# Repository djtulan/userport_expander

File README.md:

# Userport Expander
C64 Userport Expander is a remake of a project from a "64'er Sonderheft" magazine.

You can find the scan (german language) [here](./docs/UP%2024%20Leitungen_k.pdf).

The driver software can be found [here](./Software/SH67.zip).

The C64 Userport Expander expands the C64 Userport from 8 Bit to 3x8bit.

## 3D Model

## Real Picture

## Layout and PCB
The whole KiCad project is provided inside subfolder ["kicad"](./kicad).

Please feel free to order your own PCBs, Gerber files are here ["gerber"](./kicad/gerber).

I would be pleased about a small donation: [PAYPAL.ME](https://www.paypal.me/RobertGrasboeck)

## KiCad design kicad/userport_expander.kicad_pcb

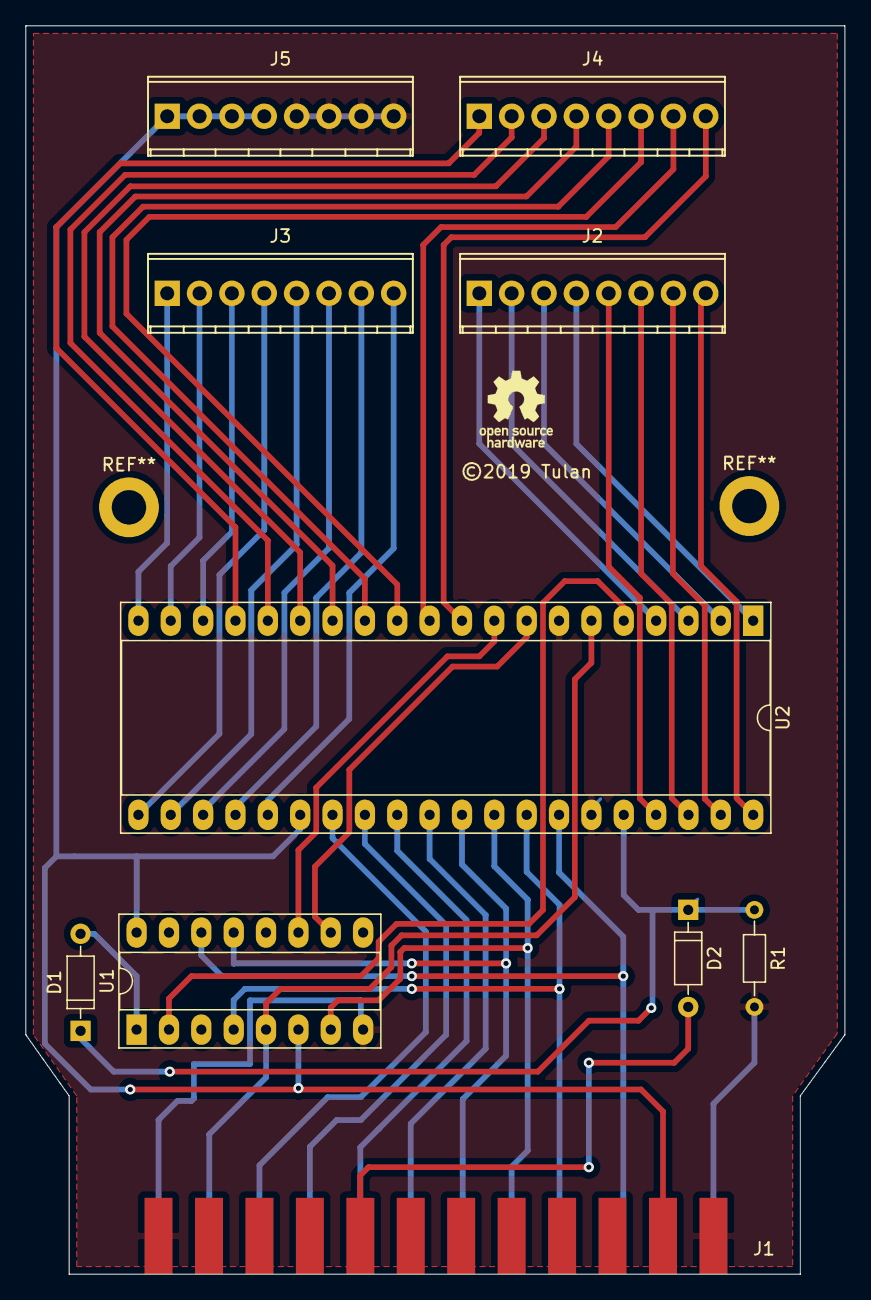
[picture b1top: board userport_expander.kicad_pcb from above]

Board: 2 copper layers, 64.3 x 98.0 mm, 10 parts (0 on the bottom side), 41 nets.

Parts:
D1, D2: 1N4148; D_DO-35_SOD27_P7.62mm_Horizontal
J1: C64-UserPort; C64-User-Port-Female
J2, J3, J4, J5: Screw_Terminal_01x08; TerminalBlock_Phoenix_MPT-2.54mm_8pol
R1: R10k; R_Axial_DIN0204_L3.6mm_D1.6mm_P7.62mm_Horizontal
U1: 4042; DIP-16_W7.62mm_Socket_LongPads
U2: 8255; DIP-40_W15.24mm_Socket_LongPads

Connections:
GND: J1.1, J1.12, J1.A, J1.N, J5.5, J5.6, J5.7, J5.8, R1.2, U1.8, U2.7, U2.35
unnamed: D1.1, D2.1, R1.1, U2.36
unnamed: D1.2, U1.1
unnamed: D2.2, J1.8
unnamed: J1.C, U1.14, U2.34
unnamed: J1.D, U1.4, U2.33
unnamed: J1.E, U1.7, U2.32
unnamed: J1.F, U1.13, U2.31
unnamed: J1.H, U2.30
unnamed: J1.J, U2.29
unnamed: J1.K, U2.28
unnamed: J1.L, U2.27
unnamed: J1.M, U1.5, U2.6
unnamed: J2.1, U2.4
unnamed: J2.2, U2.3
unnamed: J2.3, U2.2
unnamed: J2.4, U2.1
unnamed: J2.5, U2.37
unnamed: J2.6, U2.38
unnamed: J2.7, U2.39
unnamed: J2.8, U2.40
unnamed: J3.1, U2.20
unnamed: J3.2, U2.19
unnamed: J3.3, U2.18
unnamed: J3.4, U2.21
unnamed: J3.5, U2.22
unnamed: J3.6, U2.23
unnamed: J3.7, U2.24
unnamed: J3.8, U2.25
unnamed: J4.1, U2.17
unnamed: J4.2, U2.16
unnamed: J4.3, U2.15
unnamed: J4.4, U2.14
unnamed: J4.5, U2.13
unnamed: J4.6, U2.12
unnamed: J4.7, U2.11
unnamed: J4.8, U2.10
unnamed: U1.2, U2.5
unnamed: U1.10, U2.8
unnamed: U1.11, U2.9
VCC: J1.2, J5.1, J5.2, J5.3, J5.4, U1.6, U1.16, U2.26

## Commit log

2019-12-01 added folders
2019-12-01 added dimension
2019-12-01 added oshw logo
2019-12-01 fixed readme
2019-12-01 added gerbers
2019-12-01 added Software
2020-02-16 added images
2020-02-16 added doc

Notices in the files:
kicad/userport_expander.kicad_pcb:
©2019 Tulan
